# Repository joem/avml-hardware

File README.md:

AVML Hardware
=============

*KiCad projects for the AVML hardware*

This repo is the sister repo to avml-software (link TBD).
<!-- FIXME: add this link to the repo! -->

About the AVML
--------------

AVML stands for *Arduino Video Module L*, though I never really refer to it by that long name. It's a eurorack format module that uses an Arduino Nano to generate video in the [LZX patchable video format](https://lzxindustries.net). I originally made the module to be a text generator and pattern generator, but it includes several different modes by default and can be programmed to do whatever you want (within its abilities). The microcontroller at the heart of the Arduino Nano is not the most capable microcontroller, but there are a lot of Arduino programming resources out there for it. Further, since I'm using a stock (unmodified) Nano, its video capabilities are reduced to very low-res black and white, but it's a fun aesthetic to work with.

Note: While the AVML can certainly be modded to not require sync and to output composite video, it can not do those things without modification. Eventually I hope to release either mod details or a separate device/module for that, but I have not done so yet. Sorry.

Usage
-----

*to be added*
<!-- FIXME: add this info! -->
<!-- maybe link to another page somewhere? or have a usage file? -->

About the schematic
-------------------

An easily readable PDF schematic for the module is in the `pcb/pdfs/` folder.

About the PCBs/panel
--------------------

Both of the PCBs live in one KiCad project, in the `pcb` folder. There's only one schematic file, and only one PCB file. If you change them and want to export gerbers, you should save your changes, copy the `.kicad_pcb` file to a new file, then open that file in kicad and delete one of the boards before exporting gerbers. You should then delete the copied `.kicad_pcb` and the `.pro` file that kicad creates when you open it, so that you don't accidentally make changes to that instead of the main project files.

I know it's a little messy that way, but it made working with the boards easier, especially when I had to move things between boards. I tried it the "proper" one-project-per-board way and it was a pain.

The panel lives in the `panel` folder (even though it's also a PCB).

### pcb1

PCB1 is the controls board, with the jacks, switches, and buttons on it. Also since space was tight, there are some parts here that would normally have on the main board.

### pcb2

PCB2 is the main board, with the Arduino, some of the ICs, and some of the power circuits. (Some of the power and ICs ended up on PCB1 due to space constraints.)

### panel

The panel is the eurorack-format front panel. As of right now, it's nothing special, but it does have labels for all the controls. There is a minor schematic for this PCB, since I wasn't sure how to add a net to the PCB (for the fill on the back) without one. Any component footprints on the back of the panel should be ignored and not populated upon building. They are not in the official BOM, in order to hopefully avoid confusion.

BOM
---

*to be added*
<!-- FIXME: add this info! -->

This is also mentioned in the panel section but it bears repeating here: Any component footprints on the back of the panel can and should be ignored and not populated upon building.

Credits / Thanks
----------------

The AVML hardware owes its existence to several parties who may not have had direct involvement in it's development, but are still deserving of credit and thanks:

- **The Arduino TVout library author(s)** -- This is what first introduced me to video from the Arduino. It's very low res and not perfect by a long shot, but the ability to get video out of an Arduino just by using this library and adding a few passive components was amazing! Plus it's the basis for the video library the AVML uses.
- **[Nootropic Design](https://nootropicdesign.com)** -- Their [Video Experimenter shield](https://nootropicdesign.com/video-experimenter/) and [enhanced TVout library](https://github.com/nootropicdesign/arduino-tvout-ve) brought the dream of syncing the Arduino's video output to another source, without needing a pricey time base corrector. The AVML uses a further-enhanced version the the enhanced TVout library. too.
- **Émilie/[Mutable Instruments](https://mutable-instruments.net)** -- Something I learned from studying Mutable Instruments schematics or from reading her forum posts is in every single one of my electronics projects, one way or another. Most notably in the AVML, the input circuitry comes from some of the Mutable Instruments modules. 
- **Marshall Thompson** on the LZX Facebook group -- for letting me know about how to hook an Arduino (running TVout-ve) up to LZX sync. If it weren't for that simple sharing of a little info, I probably wouldn't have made this module.
- **[LZX Industries](https://lzxindustries.net/pages/about-us) and Lars Larsen in particular** -- Modular video synthesis has been a dream of mine since I was a teenager, but I never knew that's what I wanted until I discovered the LZX world. Lars (like Émilie from Mutable Instruments) has generously made many useful schematics available and is extremely generous with helping others with video electronics questions.
- **The [Arduino](https://www.arduino.cc) organization** -- The Arduino ecosystem is a wonderful thing that I wish were around when I was much younger. It's what's allowed me to release a project such as this and know that it's at least somewhat accessible to all kinds of people.
- **The [KiCad](https://www.kicad.org) creators and contributors** -- I'm so glad that KiCad exists, and without it I may never have ever tried making PCBs myself.

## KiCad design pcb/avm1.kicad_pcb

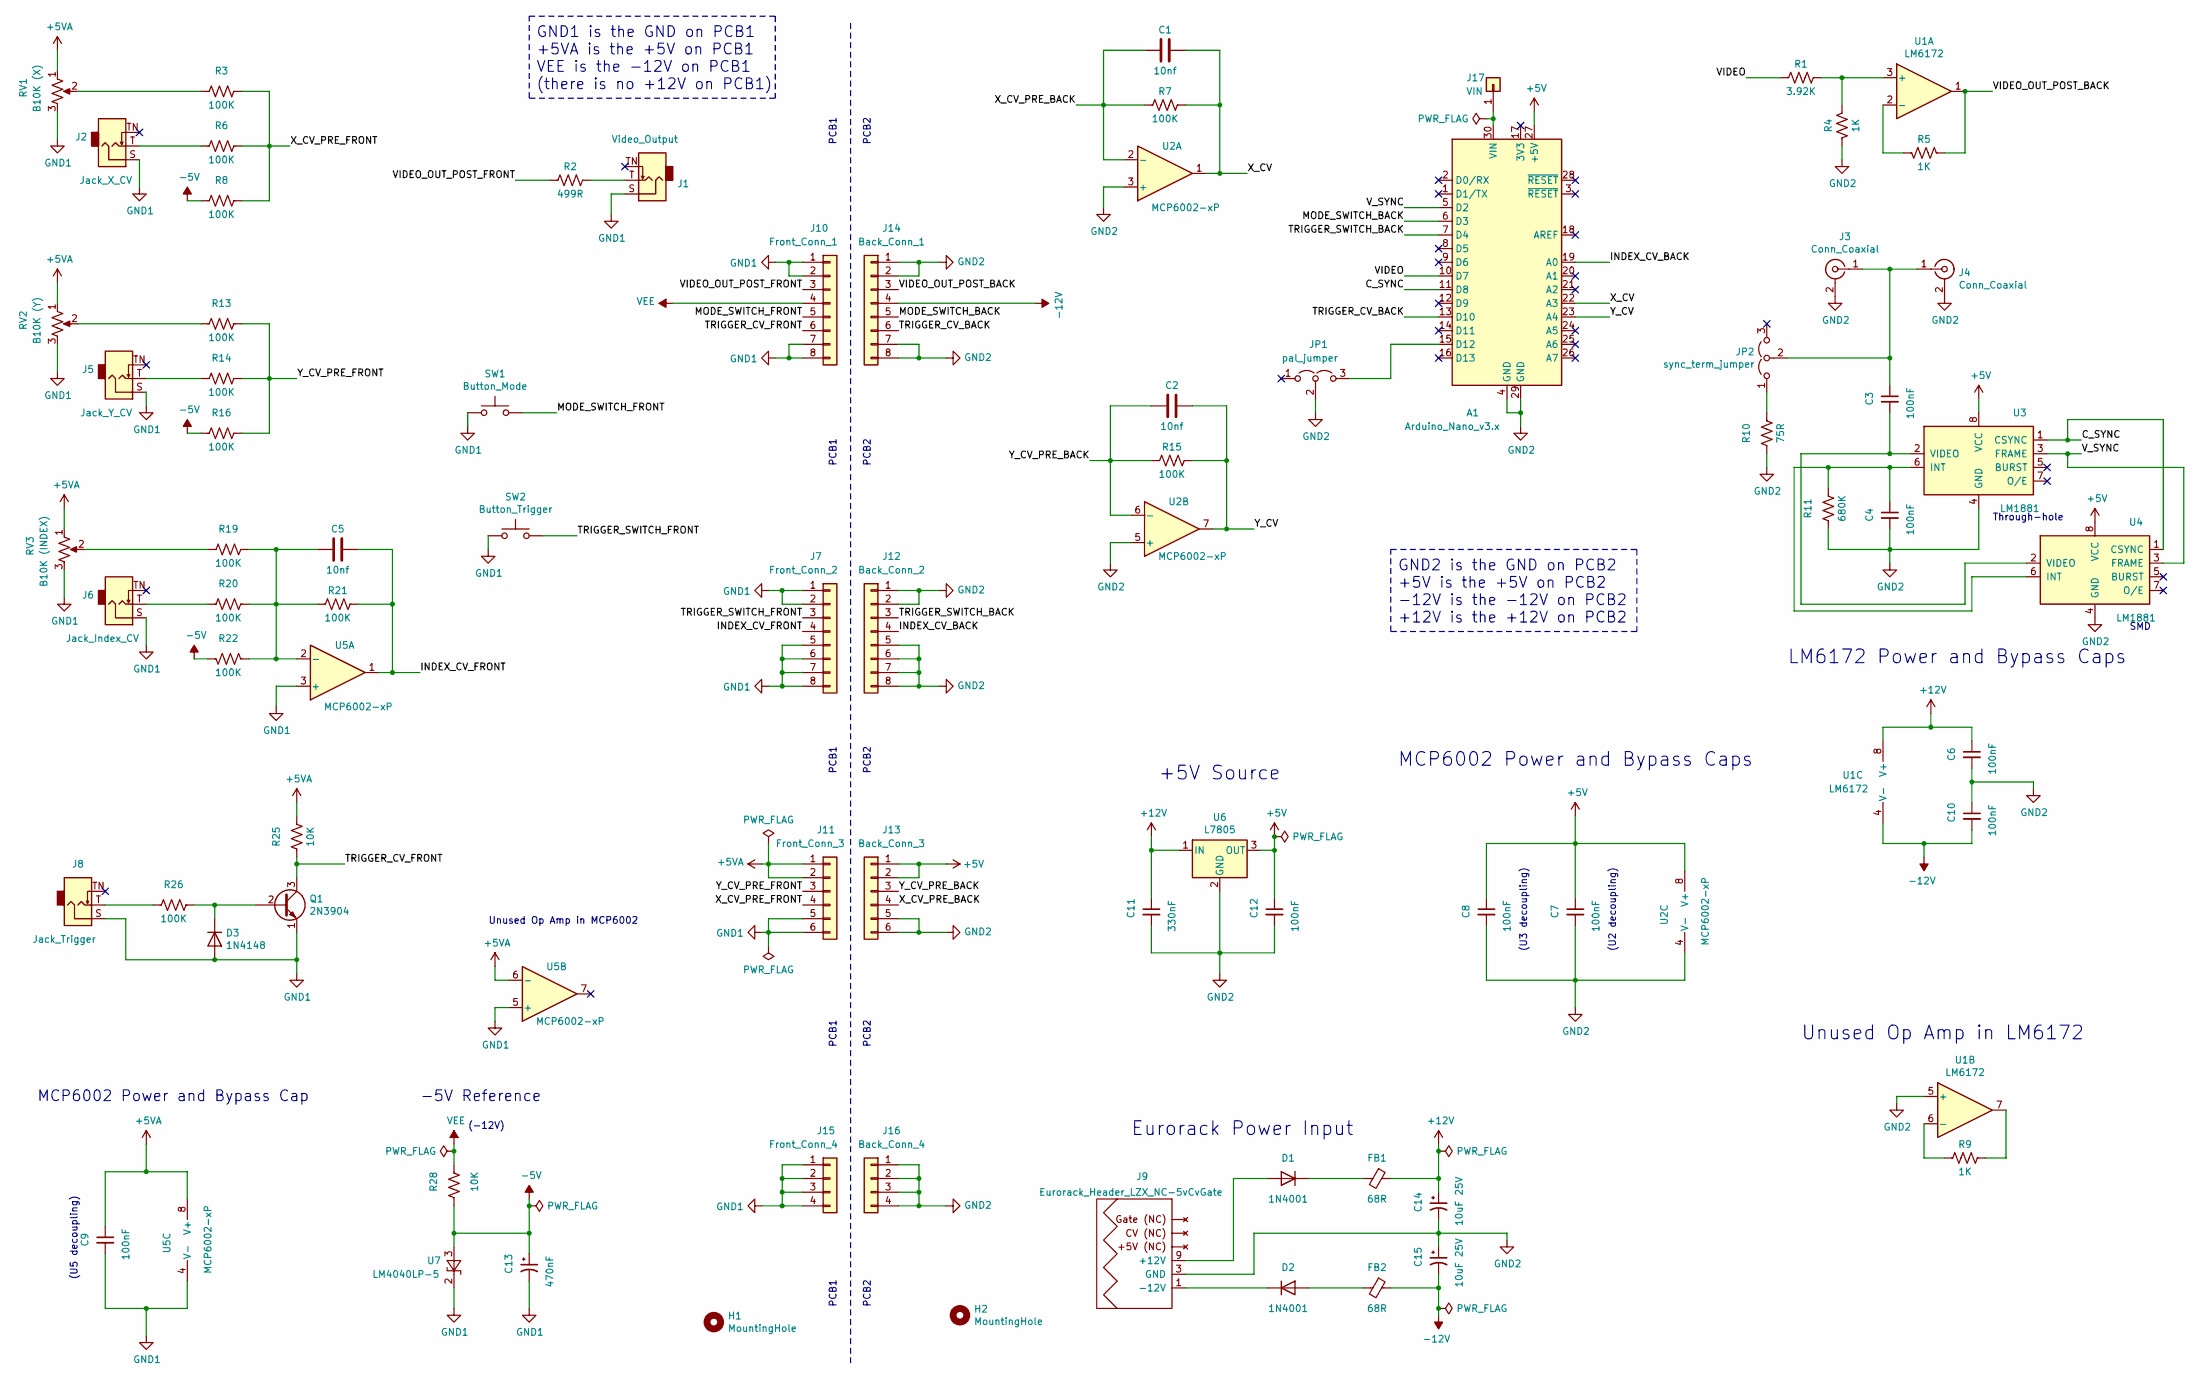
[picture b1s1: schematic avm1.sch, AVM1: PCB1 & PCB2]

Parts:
A1: Arduino_Nano_v3.x; Arduino_Nano_WithMFHeadersAnd3DModel
C1, C2, C5: 10nf; C_Disc_D5.0mm_W2.5mm_P2.50mm_LZX
C3, C4, C6, C7, C8, C9, C10, C12: 100nF; C_Disc_D5.0mm_W2.5mm_P2.50mm_LZX
C11: 330nF; C_Disc_D5.0mm_W2.5mm_P2.50mm_LZX
C13: 470nF; C_Disc_D5.0mm_W2.5mm_P2.50mm_LZX
C14, C15: 10uF 25V; CP_Radial_D5.0mm_P2.00mm_BiggerPlusSign
D1, D2: 1N4001; D_DO-41_SOD81_P10.16mm_Horizontal
D3: 1N4148; D_P7.62mm_Horizontal_LZX
FB1, FB2: 68R; R_Axial_DIN0207_L6.3mm_D2.5mm_P10.16mm_Horizontal
H1, H2: MountingHole; MountingHole_3.2mm_M3
J1: Video_Output; Jack_3.5mm_QingPu_WQP-PJ398SM_Vertical_CircularHoles_With3D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
J2: Jack_X_CV; Jack_3.5mm_QingPu_WQP-PJ398SM_Vertical_CircularHoles_With3D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
J3, J4: Conn_Coaxial; RCA-Phono_CUI-Devices_RCJ-02X_Vertical
J5: Jack_Y_CV; Jack_3.5mm_QingPu_WQP-PJ398SM_Vertical_CircularHoles_With3D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
J6: Jack_Index_CV; Jack_3.5mm_QingPu_WQP-PJ398SM_Vertical_CircularHoles_With3D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
J7: Front_Conn_2; PinHeader_1x08_P2.54mm_Vertical
J8: Jack_Trigger; Jack_3.5mm_QingPu_WQP-PJ398SM_Vertical_CircularHoles_With3D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
J9: Eurorack_Header_LZX_NC-5vCvGate; IDC-Header_2x08_P2.54mm_Vertical_EurorackPower
J10: Front_Conn_1; PinHeader_1x08_P2.54mm_Vertical
J11: Front_Conn_3; PinHeader_1x06_P2.54mm_Vertical
J12: Back_Conn_2; PinSocket_1x08_P2.54mm_Vertical
J13: Back_Conn_3; PinSocket_1x06_P2.54mm_Vertical
J14: Back_Conn_1; PinSocket_1x08_P2.54mm_Vertical
J15: Front_Conn_4; PinHeader_1x04_P2.54mm_Vertical
J16: Back_Conn_4; PinSocket_1x04_P2.54mm_Vertical
J17: VIN; SolderWire-0.5sqmm_1x01_D0.9mm_OD2.1mm
JP1: pal_jumper; PinHeader_1x03_P2.54mm_Vertical
JP2: sync_term_jumper; PinHeader_1x03_P2.54mm_Vertical
Q1: 2N3904; TO-92_Inline_Wide
R1: 3.92K; R_Axial_DIN0207_L6.3mm_D2.5mm_P2.54mm_Vertical
R2: 499R; R_Axial_P7.62mm_Horizontal_LZX
R3, R6, R7, R8, R13, R14, R16, R19, R20, R21, R22, R26: 100K; R_Axial_P7.62mm_Horizontal_LZX
R4, R5, R9: 1K; R_Axial_DIN0207_L6.3mm_D2.5mm_P2.54mm_Vertical
R10: 75R; R_Axial_P7.62mm_Horizontal_LZX
R11: 680K; R_Axial_DIN0207_L6.3mm_D2.5mm_P2.54mm_Vertical
R15: 100K; R_Axial_DIN0207_L6.3mm_D2.5mm_P2.54mm_Vertical
R25, R28: 10K; R_Axial_P7.62mm_Horizontal_LZX
RV1: B10K (X); Potentiometer_Alpha_RD901F-40-00D_Single_Vertical_CircularH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
RV2: B10K (Y); Potentiometer_Alpha_RD901F-40-00D_Single_Vertical_CircularH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
RV3: B10K (INDEX); Potentiometer_Alpha_RD901F-40-00D_Single_Vertical_CircularH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
SW1: Button_Mode; SW_PUSH_6mm_H7.3mm
SW2: Button_Trigger; SW_PUSH_6mm_H7.3mm
U1: LM6172; DIP-8_W7.62mm_MediumOffsetPads
U2: MCP6002-xP; DIP-8_W7.62mm_MediumOffsetPads
U3: LM1881; DIP-8_W7.62mm_MediumOffsetPads
U4: LM1881; SOIC-8_3.9x4.9mm_P1.27mm_LongPads
U5: MCP6002-xP; DIP-8_W7.62mm
U6: L7805; TO-220-3_Horizontal_TabDown
U7: LM4040LP-5; TO-92_Inline_Wide

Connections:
+5V: A1.27 (+5V), C7.1, C8.1, C12.1, J13.1, J13.2, U2.8 (V+), U3.8 (VCC), U4.8 (VCC), U6.3 (OUT)
+5VA: C9.1, J11.1, J11.2, R25.2, RV1.1, RV2.1, RV3.1, U5.6 (-), U5.8 (V+)
+12V: C6.1, C11.1, C14.1, FB1.1, U1.8 (V+), U6.1 (IN)
-5V: C13.1, R8.2, R16.2, R22.1, R28.2, U7.3 (A)
-12V: C10.2, C15.2, FB2.1, J14.4, U1.4 (V-)
/C_SYNC: A1.11 (D8), U3.1 (CSYNC), U4.1 (CSYNC)
/INDEX_CV_BACK: A1.19 (A0), J12.4
/INDEX_CV_FRONT: C5.1, J7.4, R21.1, U5.1
/MODE_SWITCH_BACK: A1.6 (D3), J14.5
/MODE_SWITCH_FRONT: J10.5, SW1.2
/TRIGGER_CV_BACK: A1.13 (D10), J14.6
/TRIGGER_CV_FRONT: J10.6, Q1.3 (C), R25.1
/TRIGGER_SWITCH_BACK: A1.7 (D4), J12.3
/TRIGGER_SWITCH_FRONT: J7.3, SW2.2
/VIDEO: A1.10 (D7), R1.2
/VIDEO_OUT_POST_BACK: J14.3, R5.2, U1.1
/VIDEO_OUT_POST_FRONT: J10.3, R2.2
/V_SYNC: A1.5 (D2), U3.3 (FRAME), U4.3 (FRAME)
/X_CV: A1.22 (A3), C1.1, R7.1, U2.1
/X_CV_PRE_BACK: C1.2, J13.4, R7.2, U2.2 (-)
/X_CV_PRE_FRONT: J11.4, R3.1, R6.1, R8.1
/Y_CV: A1.23 (A4), C2.1, R15.1, U2.7
/Y_CV_PRE_BACK: C2.2, J13.3, R15.2, U2.6 (-)
/Y_CV_PRE_FRONT: J11.3, R13.1, R14.1, R16.1
GND1: C9.2, C13.2, D3.2 (A), J1.S, J2.S, J5.S, J6.S, J7.1, J7.2, J7.5, J7.6, J7.7, J7.8, J8.S, J10.1, J10.2, J10.7, J10.8, J11.5, J11.6, J15.1, J15.2, J15.3, J15.4, Q1.1 (E), RV1.3, RV2.3, RV3.3, SW1.1, SW2.1, U5.3 (+), U5.4 (V-), U5.5 (+), U7.2 (K)
GND2: A1.4 (GND), A1.29 (GND), C4.2, C6.2, C7.2, C8.2, C10.1, C11.2, C12.2, C14.2, C15.1, J3.2 (Ext), J4.2 (Ext), J9.3 (GND), J9.4 (GND), J9.5 (GND), J9.6 (GND), J9.7 (GND), J9.8 (GND), J12.1, J12.2, J12.5, J12.6, J12.7, J12.8, J13.5, J13.6, J14.1, J14.2, J14.7, J14.8, J16.1, J16.2, J16.3, J16.4, JP1.2 (C), R4.1, R10.1, R11.1, U1.5 (+), U2.3 (+), U2.4 (V-), U2.5 (+), U3.4 (GND), U4.4 (GND), U6.2 (GND)
unnamed: A1.15 (D12), JP1.3 (B)
unnamed: A1.30 (VIN), J17.1
unnamed: C3.1, J3.1 (In), J4.1 (In), JP2.2 (C)
unnamed: C3.2, U3.2 (VIDEO), U4.2 (VIDEO)
unnamed: C4.1, R11.2, U3.6 (INT), U4.6 (INT)
unnamed: C5.2, R19.1, R20.1, R21.2, R22.2, U5.2 (-)
unnamed: D1.1 (K), FB1.2
unnamed: D1.2 (A), J9.9 (+12V), J9.10 (+12V)
unnamed: D2.1 (K), J9.1 (-12V), J9.2 (-12V)
unnamed: D2.2 (A), FB2.2
unnamed: D3.1 (K), Q1.2 (B), R26.1
unnamed: J1.T, R2.1
unnamed: J2.T, R6.2
unnamed: J5.T, R14.2
unnamed: J6.T, R20.2
unnamed: J8.T, R26.2
unnamed: JP2.1 (A), R10.2
unnamed: R1.1, R4.2, U1.3 (+)
unnamed: R3.2, RV1.2
unnamed: R5.1, U1.2 (-)
unnamed: R9.1, U1.7
unnamed: R9.2, U1.6 (-)
unnamed: R13.2, RV2.2
unnamed: R19.2, RV3.2
VEE: J10.4, R28.1

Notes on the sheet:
(U5 decoupling)
-5V Reference
Unused Op Amp in MCP6002
MCP6002 Power and Bypass Cap
(-12V)
Unused Op Amp in LM6172
MCP6002 Power and Bypass Caps
LM6172 Power and Bypass Caps
+5V Source
Eurorack Power Input
(U3 decoupling)
(U2 decoupling)
GND1 is the GND on PCB1 +5VA is the +5V on PCB1 VEE is the -12V on PCB1 (there is no +12V on PCB1)
PCB1
PCB2
GND2 is the GND on PCB2 +5V is the +5V on PCB2 -12V is the -12V on PCB2 +12V is the +12V on PCB2
SMD
Through-hole

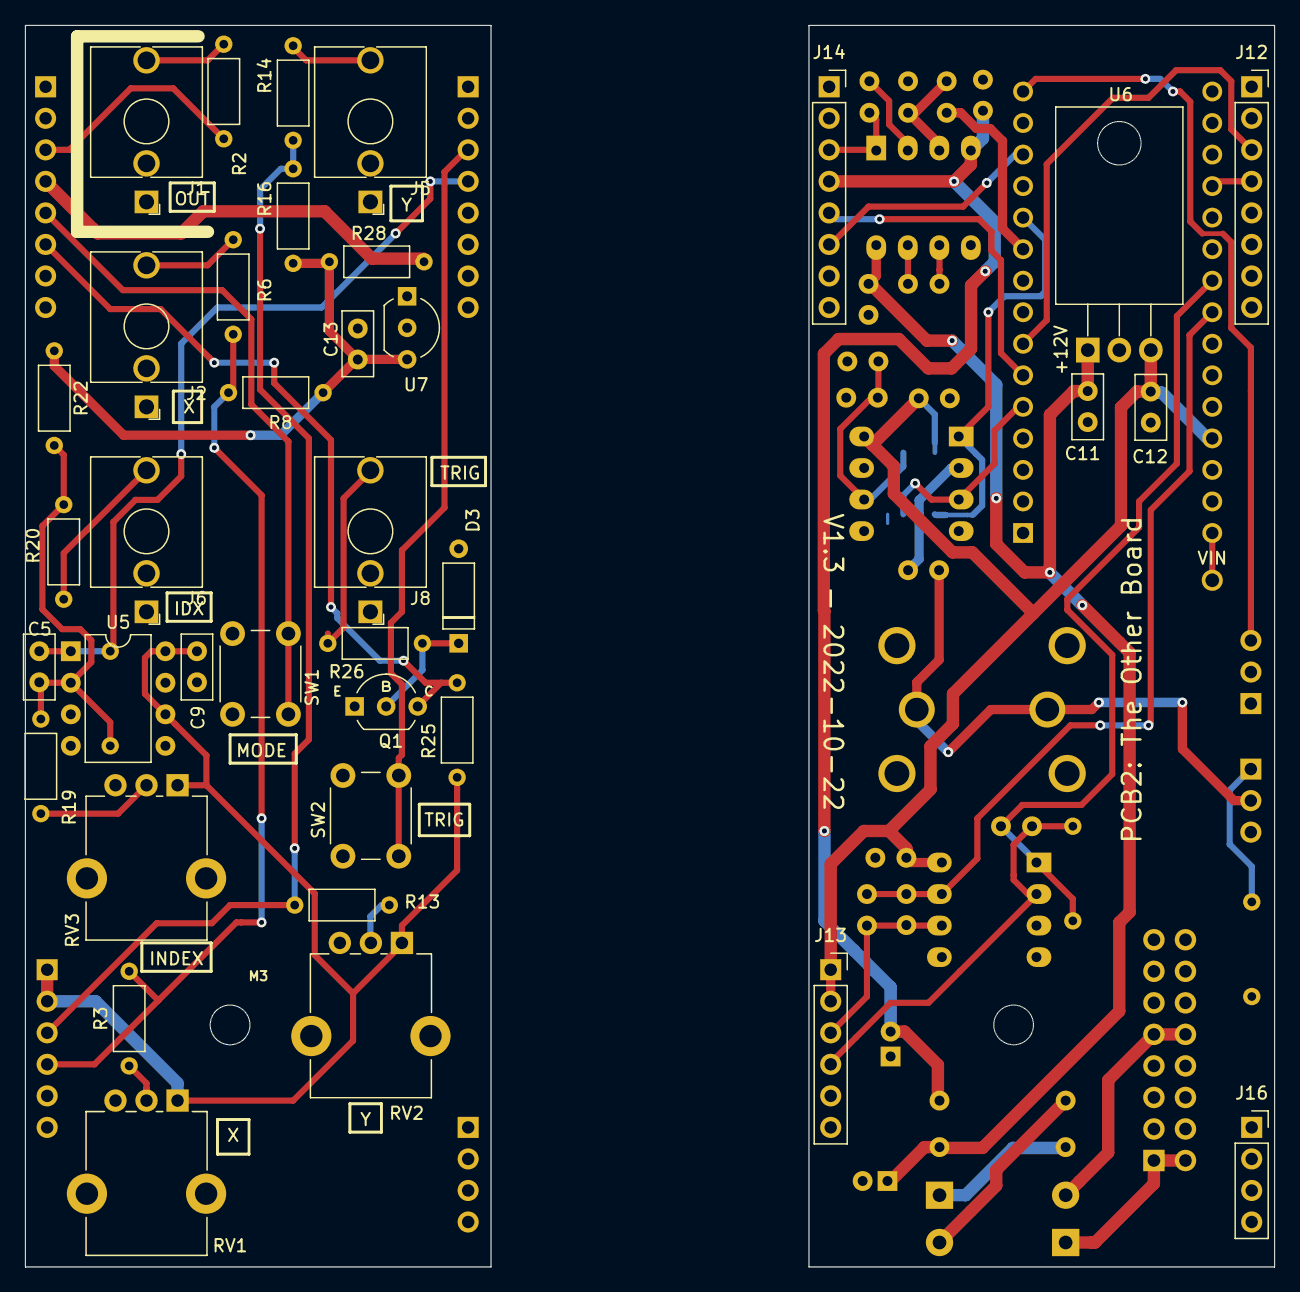
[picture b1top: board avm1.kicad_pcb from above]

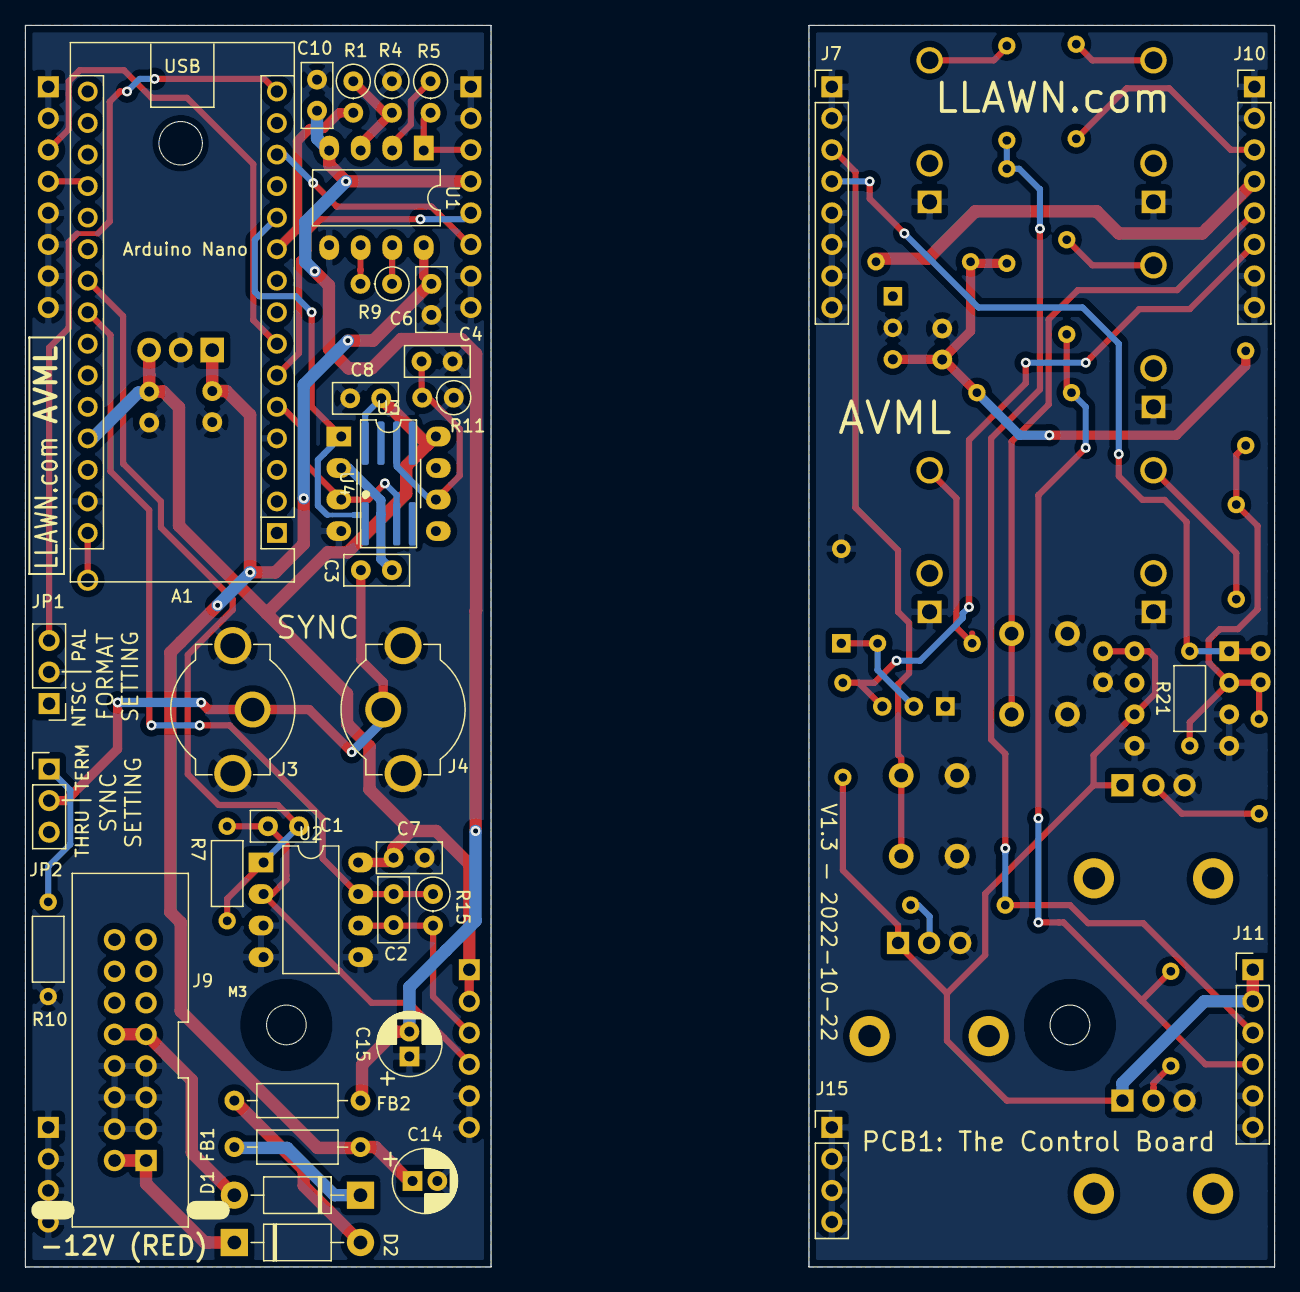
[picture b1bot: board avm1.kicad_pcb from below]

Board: 2 copper layers, 100.6 x 100.0 mm, 77 parts (38 on the bottom side), 51 nets.

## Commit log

2021-03-14 Add a combined schematic project
2021-03-14 Add readme
2021-10-24 Updated board after upgrading kicad
2021-10-24 Add render of combined schematic
2021-11-04 fix combined schematic and pcb
2021-11-04 remove separate pcb1 and pcb2
2021-11-04 move pcbs to the pcb dir
2021-11-04 Add todo note to drawings layer
2021-11-04 update schematic info and export to pdf
2021-11-04 Simplify pcb filenames
2021-11-04 Update schematic to reflect simpler name
2021-11-04 update readme again
2021-11-12 Update panel
2021-11-15 Added SMD LM1881 footprint, moved a few things around
2021-11-15 Update panel for v1.1 gerbers
2021-11-21 Neaten up the schematic a bit
2022-10-23 Update panel with new logo and minor design change
2022-10-23 Do a bunch of improvements
2022-10-23 tweaked some more things
2022-10-23 rename files for pcbs
2022-10-23 Do a few minor changes to panel
2022-10-23 rename files for panel
2022-10-23 Update readme with new name and some other changes
2022-10-23 Replace old schematic pdfs with new one
2023-01-17 Move line on panel between X and Index knobs
2023-01-22 Add note about unused sync out and audio out to schematic
2023-04-03 Update panel to kicad 6+
2023-04-03 Update pcb to kicad 6+
2023-04-03 Add gitignore
2023-04-03 Add note to readme about requiring kicad 6+
